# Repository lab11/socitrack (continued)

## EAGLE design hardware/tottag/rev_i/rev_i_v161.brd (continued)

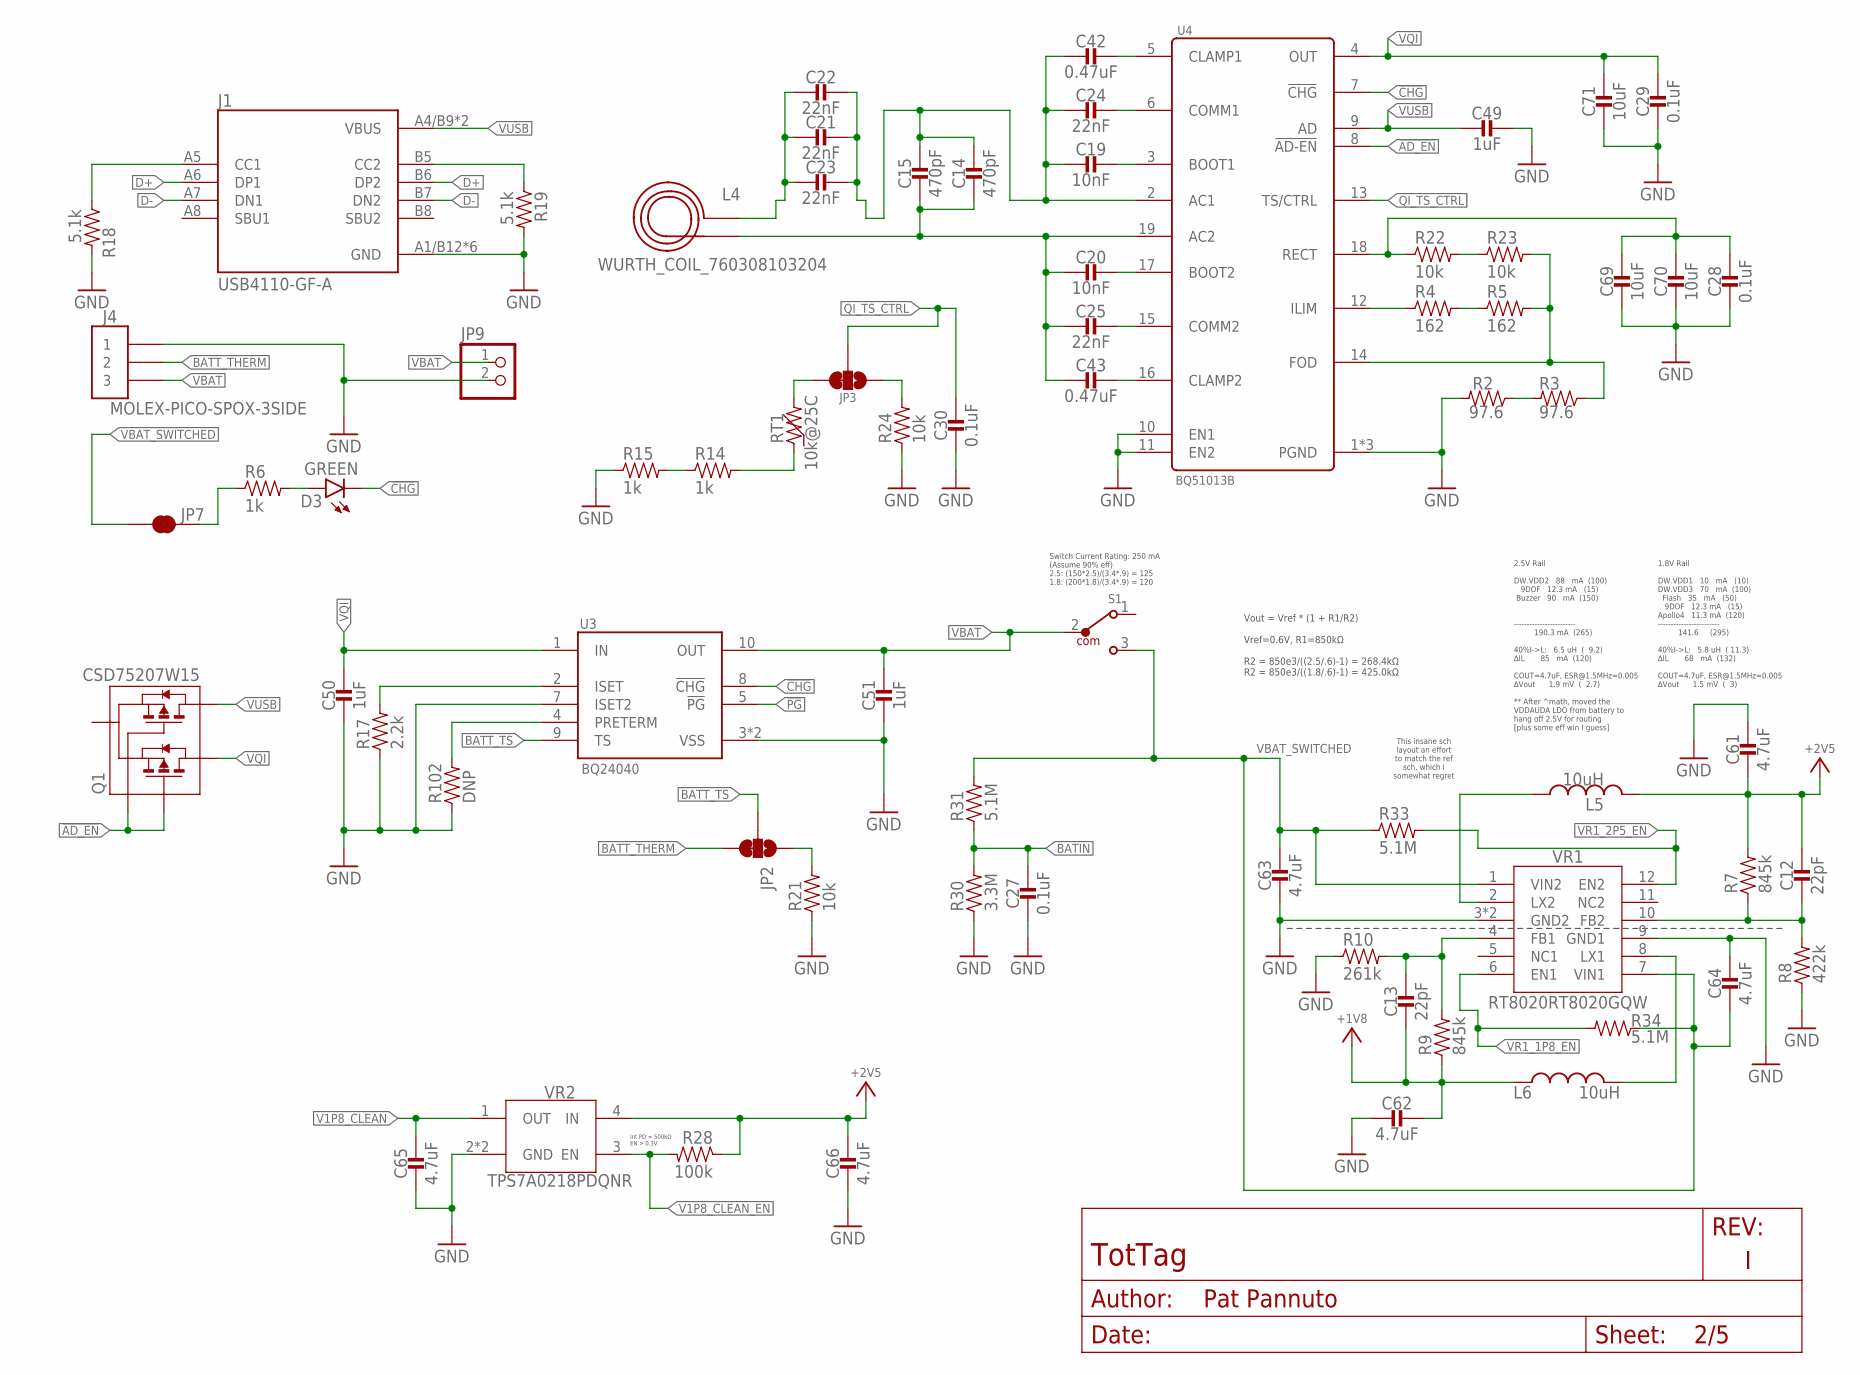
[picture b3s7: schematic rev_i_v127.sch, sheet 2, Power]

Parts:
C12, C13: 22pF; 0201_CAP; MPN GRM0335C1H220FA01D
C14, C15: 470pF; 0402_CAP; MPN GRM1555C1H471JA01J; DIGIKEY 490-6242-1-ND
C19, C20: 10nF; 0402_CAP; MPN GRM155R71H103KA88J; DIGIKEY 490-6351-2-ND
C21, C22, C23: 22nF; 0402_CAP; MPN GRM155R71E223JA61D; DIGIKEY 490-10699-2-ND
C24, C25: 22nF; 0402_CAP; MPN CC0402ZRY5V8BB223; DIGIKEY 311-3823-1-ND
C27, C28, C29, C30: 0.1uF; 0402_CAP; MPN GRM155R71C104KA88J; DIGIKEY 490-6328-1-ND
C42, C43: 0.47uF; 0402_CAP; MPN GRT155R61E474ME01D; DIGIKEY 490-12270-1-ND
C49, C50, C51: 1uF; 0402_CAP; MPN GRM155R70G105KA12D; DIGIKEY 490-7195-1-ND
C61, C62, C63, C64, C65, C66: 4.7uF; 0805_CAP; MPN JMK212ABJ475MGHT
C69, C70, C71: 10uF; 0603_CAP; MPN CM105X5R106M25AT; DIGIKEY 1253-CM105X5R106M25ATCT-ND
D3: GREEN; LED-0603; MPN LTST-C191KGKT; DIGIKEY 160-1446-1-ND
J1: USB4110-GF-A; GCT_USB4110-GF-A
J4: MOLEX-PICO-SPOX-3SIDE; MOLEX-PICO-SPOX-3_SIDE
JP2, JP3: JUMPER-SMT_3_1-NC_TRACE_SILK; SMT-JUMPER_3_1-NC_TRACE_SILK
JP7: JUMPER-SMT_2_NC_TRACE_SILK; SMT-JUMPER_2_NC_TRACE_SILK
JP9: PINHD-1X2; 1X02
L4: WURTH_COIL_760308103204
L5, L6: 10uH; NRX3015; MPN NR3015T100M
Q1: CSD75207W15; DSBGA
R2, R3: 97.6; 0402_RES; MPN RMCF0402FT97R6; DIGIKEY RMCF0402FT97R6CT-ND
R4, R5: 162; 0402_RES; MPN RMCF0402FT162R; DIGIKEY RMCF0402FT162RCT-ND
R6, R14, R15: 1k; 0402_RES
R7, R9: 845k; 0201_RES; MPN ERJ-1GNF8453C
R8: 422k; 0201_RES; MPN ERJ-1GNF4223C
R10: 261k; 0201_RES; MPN ERJ-1GNF2613C
R17: 2.2k; 0402_RES; MPN RMCF0402JT2K20; DIGIKEY RMCF0402JT2K20CT-ND
R18, R19: 5.1k; 0402_RES; MPN RMCF0402FT5K10; DIGIKEY RMCF0402FT5K10CT-ND
R21, R22, R23, R24: 10k; 0402_RES; MPN RC0402JR-0710KL; DIGIKEY 311-10KJRCT-ND
R28: 100k; 0402_RES; MPN RT0402BRE07100KL
R30: 3.3M; 0402_RES; MPN RMCF0402FT3M30; DIGIKEY RMCF0402FT3M30CT-ND
R31, R33, R34: 5.1M; 0402_RES; MPN RMCF0402FT5M10; DIGIKEY RMCF0402FT5M10CT-ND
R102: DNP; 0402_RES
RT1: 10k@25C; 0402_RES; MPN NCU15XH103F60RC; DIGIKEY 490-18149-1-ND
S1: 450404015514; DIGIKEY 732-13665-1-ND
U3: BQ24040; DSQ0010A
U4: BQ51013B; RHL0020A
VR1: RT8020RT8020GQW; SON45P300X300X80-13T160X250N
VR2: TPS7A0218PDQNR; 4-XDFN-EP

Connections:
!AD_EN: Q1.A1 (G1), Q1.C1 (G2), U4.8 (!AD-EN)
!CHG: D3.C, U3.8 (!CHG), U4.7 (!CHG); also elsewhere on the board
!PG: U3.5 (!PG); also elsewhere on the board
+1V8: C13.P$2 (2), C62.P$1 (1), L6.P$1 (1), R9.1; also elsewhere on the board
+2V5: C12.P$1 (1), C61.P$2 (2), C66.P$1 (1), L5.P$2 (2), R7.2, R28.1, VR2.4 (IN); also elsewhere on the board
BATIN: C27.1, R30.2, R31.1; also elsewhere on the board
BATT_THERM: J4.2, J4.2SUPP (2), JP2.3
BATT_TS: JP2.2, U3.9 (TS)
BQ_AC1: C14.1, C15.1, C19.2, C21.1, C22.1, C23.1, C24.2, C42.2, U4.2 (AC1)
BQ_AC2: C14.2, C15.2, C20.2, C25.2, C43.2, L4.P$2 (2), U4.19 (AC2)
BQ_BOOT1: C19.1, U4.3 (BOOT1)
BQ_BOOT2: C20.1, U4.17 (BOOT2)
BQ_CLAMP1: C42.1, U4.5 (CLAMP1)
BQ_CLAMP2: C43.1, U4.16 (CLAMP2)
BQ_COMM1: C24.1, U4.6 (COMM1)
BQ_COMM2: C25.1, U4.15 (COMM2)
BQ_FOD: R3.1, R5.2, R23.2, U4.14 (FOD)
BQ_ILM: R4.1, U4.12 (ILIM)
BQ_ISET: R17.2, U3.2 (ISET)
BQ_RECT: C28.1, C69.1, C70.1, R22.1, U4.18 (RECT)
COIL_AC1: C21.2, C22.2, C23.2, L4.P$1 (1)
D+: J1.A6 (DP1), J1.B6 (DP2)
D-: J1.A7 (DN1), J1.B7 (DN2)
GND: C27.2, C28.2, C29.2, C30.2, C49.1, C50.2, C51.2, C61.P$1 (1), C62.P$2 (2), C63.P$2 (2), C64.P$1 (1), C65.P$2 (2), C66.P$2 (2), C69.2, C70.2, C71.2, J1.A1/B12 (GND), J1.B1/A12 (GND), J1.S1 (GND), J1.S2 (GND), J1.S3 (GND), J1.S4 (GND), J4.1, J4.1SUPP (1), JP9.2, R2.2, R8.1, R10.1, R15.1, R17.1, R18.2, R19.2, R21.1, R24.1, R30.1, R102.1, U3.3 (VSS), U3.7 (ISET2), U3.PAD (VSS), U4.1 (PGND), U4.10 (EN1), U4.11 (EN2), U4.20 (PGND), U4.PAD (PGND), VR1.3 (GND2), VR1.9 (GND1), VR1.13 (GND2), VR2.2 (GND), VR2.PAD (GND); also elsewhere on the board
unnamed: J1.B5 (CC2), R19.1
unnamed: J1.A5 (CC1), R18.1
unnamed: R2.1, R3.2
unnamed: JP2.1, R21.2
unnamed: R102.2, U3.4 (PRETERM)
unnamed: D3.A, R6.2
unnamed: R22.2, R23.1
unnamed: R4.2, R5.1
unnamed: JP3.1, R24.2
unnamed: JP3.3, RT1.2
unnamed: R14.2, RT1.1
unnamed: R14.1, R15.2
QI_TS_CTRL: C30.1, JP3.2, U4.13 (TS/CTRL); also elsewhere on the board
V1P8_CLEAN: C65.P$1 (1), VR2.1 (OUT); also elsewhere on the board
V1P8_CLEAN_EN: R28.2, VR2.3 (EN); also elsewhere on the board
VBAT: C51.1, J4.3, J4.3SUPP (3), JP9.1, S1.2, U3.10 (OUT)
VBAT_SWITCHED: C63.P$1 (1), C64.P$2 (2), JP7.1, R31.2, R33.1, R34.1, S1.3, VR1.1 (VIN2), VR1.7 (VIN1); also elsewhere on the board
VBAT_SW_FOR_CHGLED: JP7.2, R6.1
VQI: C29.1, C50.1, C71.1, Q1.A2 (D1), Q1.A3 (D1), Q1.B3 (D1), U3.1 (IN), U4.4 (OUT)
VR1_1P8_EN: R34.2, VR1.6 (EN1)
VR1_2P5_EN: R33.2, VR1.12 (EN2); also elsewhere on the board
VR1_FB1: C13.P$1 (1), R9.2, R10.2, VR1.4 (FB1)
VR1_FB2: C12.P$2 (2), R7.1, R8.2, VR1.10 (FB2)
VR1_LX1: L6.P$2 (2), VR1.8 (LX1)
VR1_LX2: L5.P$1 (1), VR1.2 (LX2)
VUSB: C49.2, J1.A4/B9 (VBUS), J1.B4/A9 (VBUS), Q1.B2 (D2), Q1.C2 (D2), Q1.C3 (D2), U4.9 (AD)

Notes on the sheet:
2.5V Rail DW.VDD2 88 mA (100) 9DOF 12.3 mA (15) Buzzer 90 mA (150) ------------------------ 190.3 mA (265) 40%I->L: 6.5 uH ( 9.2) ∆IL 85 mA (120) COUT=4.7uF, ESR@1.5MHz=0.005 ∆Vout 1.9 mV ( 2.7) ** After ^math, moved the VDDAUDA LDO from battery to hang off 2.5V for routing [plus some eff win I gue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
1.8V Rail DW.VDD1 10 mA (10) DW.VDD3 70 mA (100) Flash 35 mA (50) 9DOF 12.3 mA (15) Apollo4 11.3 mA (120) ------------------------ 141.6 (295) 40%I->L: 5.8 uH ( 11.3) ∆IL 68 mA (132) COUT=4.7uF, ESR@1.5MHz=0.005 ∆Vout 1.5 mV ( 3)
Vout = Vref * (1 + R1/R2) Vref=0.6V, R1=850kΩ R2 = 850e3/((2.5/.6)-1) = 268.4kΩ R2 = 850e3/((1.8/.6)-1) = 425.0kΩ
This insane sch layout an effort to match the ref sch, which I somewhat regret
Int PD = 500kΩ EN > 0.3V
Switch Current Rating: 250 mA (Assume 90% eff) 2.5: (150*2.5)/(3.4*.9) = 125 1.8: (200*1.8)/(3.4*.9) = 120

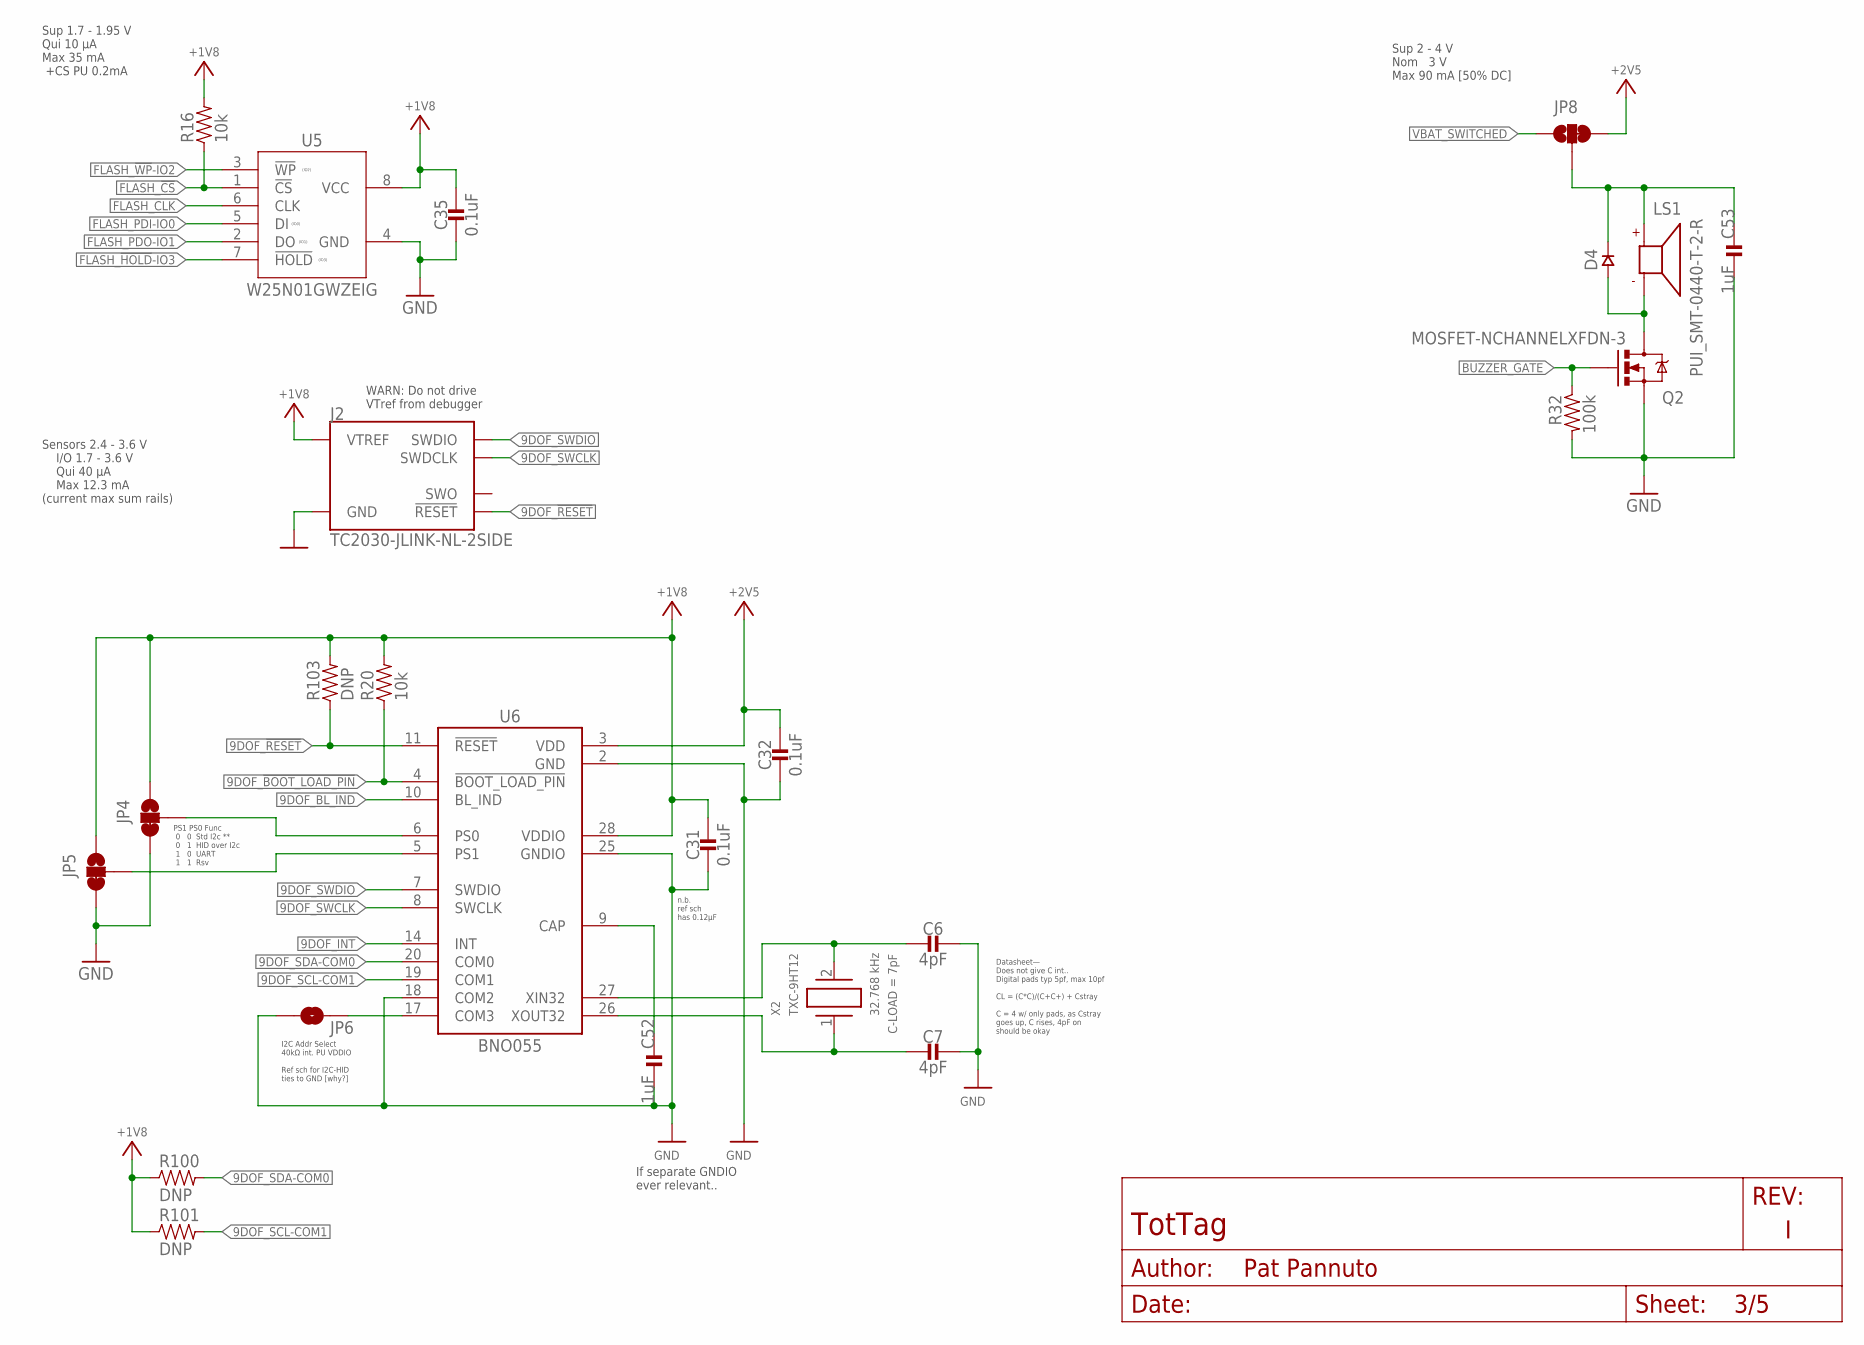
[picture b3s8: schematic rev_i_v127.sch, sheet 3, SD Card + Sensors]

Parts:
C6, C7: 4pF; 0201_CAP; MPN GRM0335C1H4R0BA01D
C31, C32, C35: 0.1uF; 0402_CAP; MPN CL05A104KP5NNNC
C52, C53: 1uF; 0201_CAP; MPN GRM033R61A105ME44D
D4: DIODE0402; 0402_DIODE; MPN CDSQR400B-HF; DIGIKEY 641-2087-1-ND
J2: TC2030-JLINK-NL-2SIDE; TC2030-IDC-NL-2SIDE
JP4, JP5, JP8: JUMPER-SMT_3_1-NC_TRACE_SILK; SMT-JUMPER_3_1-NC_TRACE_SILK
JP6: JUMPER-SMT_2_NO_SILK; SMT-JUMPER_2_NO_SILK
LS1: PUI_SMT-0440-T-2-R; SMT-0440-T-2-R
Q2: MOSFET-NCHANNELXFDN-3; XFDFN-3
R16, R20: 10k; 0402_RES; MPN RC0402JR-0710KL; DIGIKEY 311-10KJRCT-ND
R32: 100k; 0402_RES; MPN RT0402BRE07100KL
R100, R101, R103: DNP; 0603-RES
U5: W25N01GWZEIG; WSON127P800X600X80-9T430X340N
U6: BNO055; LGA28R0P510X4_5P2X3P8X1
X2: TXC-9HT12; MPN 9HT12-32.768KDZY-T

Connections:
9DOF_!BOOT_LOAD_PIN: R20.1, U6.4 (!BOOT_LOAD_PIN); also elsewhere on the board
9DOF_!RESET: J2.3 (!RESET), J2.B3 (!RESET), R103.1, U6.11 (!RESET); also elsewhere on the board
9DOF_BL_IND: U6.10 (BL_IND); also elsewhere on the board
9DOF_CAP: C52.P$1 (1), U6.9 (CAP)
9DOF_INT: U6.14 (INT); also elsewhere on the board
9DOF_SCL-COM1: R101.2, U6.19 (COM1); also elsewhere on the board
9DOF_SDA-COM0: R100.2, U6.20 (COM0); also elsewhere on the board
9DOF_SWCLK: J2.4 (SWDCLK), J2.B4 (SWDCLK), U6.8 (SWCLK)
9DOF_SWDIO: J2.2 (SWDIO), J2.B2 (SWDIO), U6.7 (SWDIO)
9DOF_XI: C6.P$2 (2), U6.27 (XIN32), X2.2
9DOF_XO: C7.P$2 (2), U6.26 (XOUT32), X2.1
+1V8: C31.1, C35.1, J2.1 (VTREF), J2.B1 (VTREF), JP4.1, JP5.1, R16.2, R20.2, R100.1, R101.1, R103.2, U5.8 (VCC), U6.28 (VDDIO); also elsewhere on the board
+2V5: C32.1, JP8.3, U6.3 (VDD); also elsewhere on the board
BUZZER_GATE: Q2.G, R32.1; also elsewhere on the board
BUZZER_SUPPLY: C53.P$1 (1), D4.CATHODE, JP8.2, LS1.+
FLASH_!CS: R16.1, U5.1 (!CS); also elsewhere on the board
FLASH_!HOLD!-IO3: U5.7 (!HOLD); also elsewhere on the board
FLASH_!WP!-IO2: U5.3 (!WP); also elsewhere on the board
FLASH_CLK: U5.6 (CLK); also elsewhere on the board
FLASH_PDI-IO0: U5.5 (DI); also elsewhere on the board
FLASH_PDO-IO1: U5.2 (DO); also elsewhere on the board
GND: C6.P$1 (1), C7.P$1 (1), C31.2, C32.2, C35.2, C52.P$2 (2), C53.P$2 (2), J2.5 (GND), J2.B5 (GND), JP4.3, JP5.3, JP6.1, Q2.S, R32.2, U5.4 (GND), U6.2 (GND), U6.18 (COM2), U6.25 (GNDIO); also elsewhere on the board
unnamed: D4.ANODE, LS1.- (N), Q2.D
unnamed: JP4.2, U6.6 (PS0)
unnamed: JP5.2, U6.5 (PS1)
unnamed: JP6.2, U6.17 (COM3)
VBAT_SWITCHED: JP8.1; also elsewhere on the board

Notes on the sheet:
Sup 1.7 - 1.95 V Qui 10 µA Max 35 mA +CS PU 0.2mA
Sensors 2.4 - 3.6 V I/O 1.7 - 3.6 V Qui 40 µA Max 12.3 mA (current max sum rails)
Sup 2 - 4 V Nom 3 V Max 90 mA [50% DC]
PS1 PS0 Func 0 0 Std I2c ** 0 1 HID over I2c 1 0 UART 1 1 Rsv
If separate GNDIO ever relevant..
I2C Addr Select 40kΩ int. PU VDDIO Ref sch for I2C-HID ties to GND [why?]
n.b. ref sch has 0.12µF
WARN: Do not drive VTref from debugger
Datasheet— Does not give C int.. Digital pads typ 5pf, max 10pf CL = (C*C)/(C+C+) + Cstray C = 4 w/ only pads, as Cstray goes up, C rises, 4pF on should be okay

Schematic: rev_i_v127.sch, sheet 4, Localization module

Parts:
A1, A2, A3: ACR0301U
C3: 2pF; 0201_CAP; MPN CBR02C209A5GAC
C10, C11: 12pF; 0402_CAP; MPN CBR04C120F5GAC; DIGIKEY 399-8815-2-ND
C16, C17, C18: 4.7nF; 0402_CAP; MPN C0402C472K3RAC7867
C33, C34, C36, C37, C38, C39: 0.1uF; 0402_CAP; MPN CL05A104KP5NNNC
C40, C41: 0.22uF; 0402_CAP; MPN CL05A224KP5NNNC
C67, C68: 4.7uF; 0402_CAP; MPN CL05A475MP5NRNC
C72, C73: 10uF; 0603_CAP; MPN CM105X5R106M25AT; DIGIKEY 1253-CM105X5R106M25ATCT-ND
FB1: BLM03PG330SN1D; 0201_FB; MPN BLM03PG330SN1D
R1: 49.9-1%; 0201_RES; MPN ERJ-1GNF49R9C
R29: 100k; 0402_RES; MPN RT0402BRE07100KL
S2: SKY13373
S3: SIP3241XSIP32414; TDFN2X2X0P6-8
TP0, TP1, TP2, TP3, TP4, TP5, TP6, TP7: TEST-POINT; PAD.03X.03
U2: DW3210; QFN40P500X500X80-40N
X4: 38.4MHz; FA-20H; MPN FA-20H 38.4000MF10Z-AS3; DIGIKEY SER3631CT-ND

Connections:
!DW_RST: U2.33 (!RST); also elsewhere on the board
!DW_SPI_CS: U2.37 (!SPICS); also elsewhere on the board
+1V8: C41.1, C68.2, S3.4 (IN), U2.29 (VDD1); also elsewhere on the board
+2V5: C34.1, C67.2, S2.6 (VDD), S3.1 (IN); also elsewhere on the board
DW_EXTON: S3.2 (CTL), S3.3 (CTL), U2.31 (EXTON)
DW_GPIO4: TP4.P$1, U2.8 (GPIO4/EXTPA)
DW_GPIO5: TP5.P$1, U2.5 (GPIO5/EXTTXE/SPIPOL)
DW_GPIO6: TP6.P$1, U2.2 (GPIO6/EXTRXE/SPIPHA)
DW_IRQ: R29.2, U2.1 (IRQ/GPIO8); also elsewhere on the board
DW_RF1: C3.P$1 (1), U2.18 (RF1)
DW_RF2: R1.1, U2.13 (RF2)
DW_RXLED: TP2.P$1, U2.6 (GPIO2/RXLED)
DW_RXOKLED: TP0.P$1, U2.3 (GPIO0/RXOKLED)
DW_SFDLED: TP1.P$1, U2.4 (GPIO1/SFDLED)
DW_SPI_CIPO: U2.36 (SPICDO(MISO)); also elsewhere on the board
DW_SPI_CLK: U2.34 (SPICLK); also elsewhere on the board
DW_SPI_COPI: U2.35 (SPICDI(MOSI)); also elsewhere on the board
DW_SYNC: TP7.P$1, U2.9 (GPIO7/SYNC)
DW_TXLED: TP3.P$1, U2.7 (GPIO3/TXLED)
DW_VDD2A: C16.1, FB1.P$2, U2.28 (VDD2A)
DW_VDD2_SUP: C17.1, C33.1, C37.1, C73.1, FB1.P$1, S3.8 (OUT), U2.23 (VDD2B)
DW_VDD3_SUP: C18.1, C36.1, C39.1, C72.1, S3.5 (OUT), U2.26 (VDD3)
DW_VIO_D: C38.1, U2.38 (VIO_D)
DW_VTX_D: C40.1, U2.27 (VTX_D)
DW_WAKEUP: U2.32 (WAKEUP); also elsewhere on the board
DW_XTI: C11.1, U2.21 (XTI), X4.3 (2)
DW_XTO: C10.1, U2.22 (XTO), X4.1
GND: C10.2, C11.2, C16.2, C17.2, C18.2, C33.2, C34.2, C36.2, C37.2, C38.2, C39.2, C40.2, C41.2, C67.1, C68.1, C72.2, C73.2, R1.2, R29.1, S2.2 (GND), S2.7 (GND), S2.8 (GND), S2.10 (GND), S2.12 (GND), S2.PAD (GND), S3.6 (GND), S3.7 (GND), S3.PAD (GND), U2.10 (GND-RF), U2.11 (GND-RF), U2.12 (GND-RF), U2.14 (GND-RF), U2.15 (GND-RF), U2.16 (GND-RF), U2.17 (GND-RF), U2.19 (GND-RF), U2.20 (GND-RF), U2.24 (VSS2), U2.25 (VSS3), U2.30 (VSS1), U2.39 (VSS), U2.40 (VSS), X4.2 (GND), X4.4 (GND); also elsewhere on the board
RF1: A1.FEED, S2.9 (J2)
RF2: A2.FEED, S2.3 (J3)
RF3: A3.FEED, S2.1 (J1)
RFC: C3.P$2 (2), S2.11 (RFC)
RFSW_V1: S2.4 (V1); also elsewhere on the board
RFSW_V2: S2.5 (V2); also elsewhere on the board

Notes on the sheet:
Supply 2.4 - 3.6 V ds #'s @ 3.0 V min typ max VDD1 1.6 3.0 3.6 VDD2a,b 2.4 3.0 3.6 VDD3 1.5 3.0 3.6 Voltage on GPIO0-5, WAKEUP, RSTn, SPICSn, SPIMOSI, SPICLK -> Max: VDD1+0.3V I/O current (max): 10 mA VDD1 -> I/O Peak cont current is RX CH9: 88 mA TX worst-case: VDD2a/b: 20 mA VDD3: 20 mA RX worst-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
SupV 2.5-4.8 I/O V 1.65-min(3.3,SupV) Active: 60 µA Qui: 5 µA
V1 V2 State 0 0 Shutdown 1 0 RFC<>J2 0 1 RFC<>J1 1 1 RFC<>J3

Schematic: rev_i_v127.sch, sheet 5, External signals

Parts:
FD1, FD2, FD3: FIDUCIAL1X2; FIDUCIAL-1X2
TP8, TP9, TP10, TP11, TP12, TP13, TP14, TP15, TP16, TP17, TP18, TP19, TP20: TEST-POINT; PAD.03X.03
TP_DW_CIPO: TPTP06SQ; TP06SQ
TP_DW_COPI: TPTP06SQ; TP06SQ
TP_DW_SPI_CLK: TPTP06SQ; TP06SQ
TP_DW_SPI_CS: TPTP06SQ; TP06SQ

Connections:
9DOF_INT: TP17.P$1; also elsewhere on the board
9DOF_SCL-COM1: TP18.P$1; also elsewhere on the board
9DOF_SDA-COM0: TP19.P$1; also elsewhere on the board
!DW_SPI_CS: TP_DW_SPI_CS.TP; also elsewhere on the board
AP4_LED1_GREEN: TP10.P$1; also elsewhere on the board
AP4_LED1_RED: TP20.P$1; also elsewhere on the board
AP4_LED2_RED: TP11.P$1; also elsewhere on the board
AP4_LED2_YELLOW: TP12.P$1; also elsewhere on the board
DW_SPI_CIPO: TP_DW_CIPO.TP; also elsewhere on the board
DW_SPI_CLK: TP_DW_SPI_CLK.TP; also elsewhere on the board
DW_SPI_COPI: TP_DW_COPI.TP; also elsewhere on the board
FLASH_!CS: TP8.P$1; also elsewhere on the board
FLASH_!HOLD!-IO3: TP16.P$1; also elsewhere on the board
FLASH_!WP!-IO2: TP15.P$1; also elsewhere on the board
FLASH_CLK: TP9.P$1; also elsewhere on the board
FLASH_PDI-IO0: TP13.P$1; also elsewhere on the board
FLASH_PDO-IO1: TP14.P$1; also elsewhere on the board

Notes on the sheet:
Miscellany
Fiducials

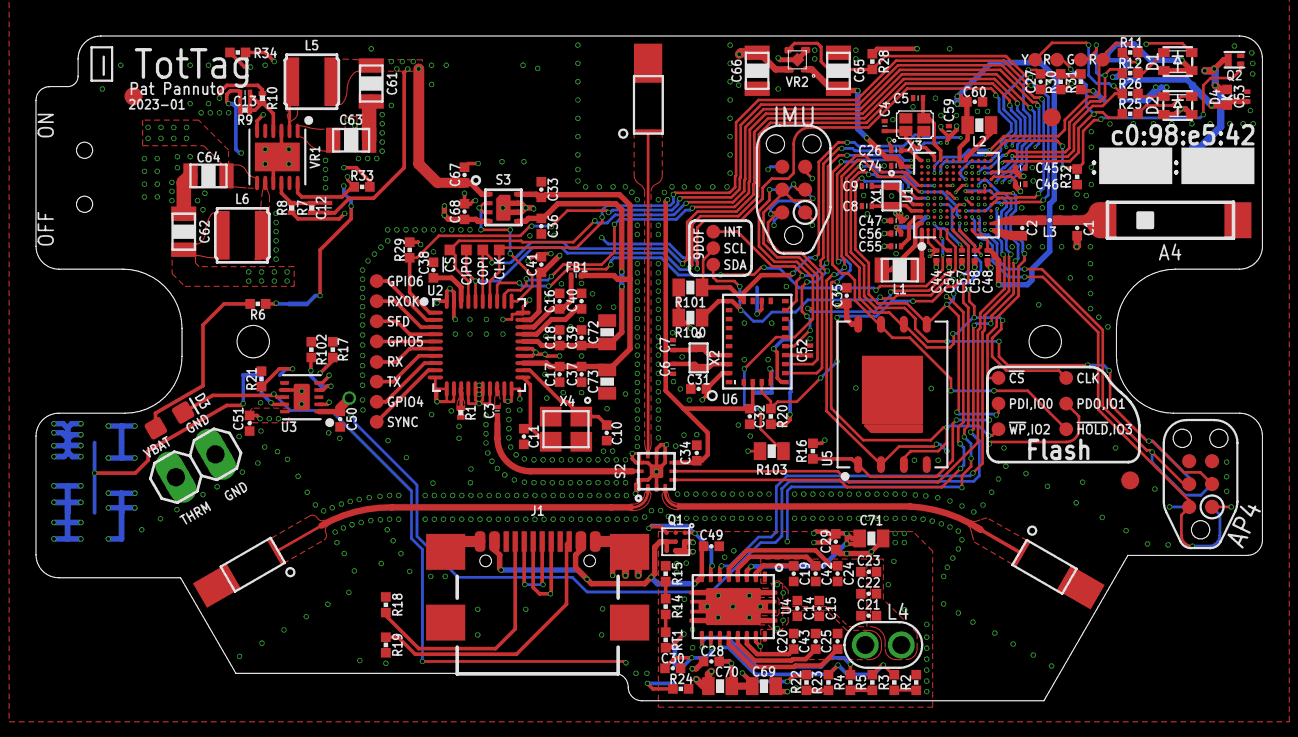
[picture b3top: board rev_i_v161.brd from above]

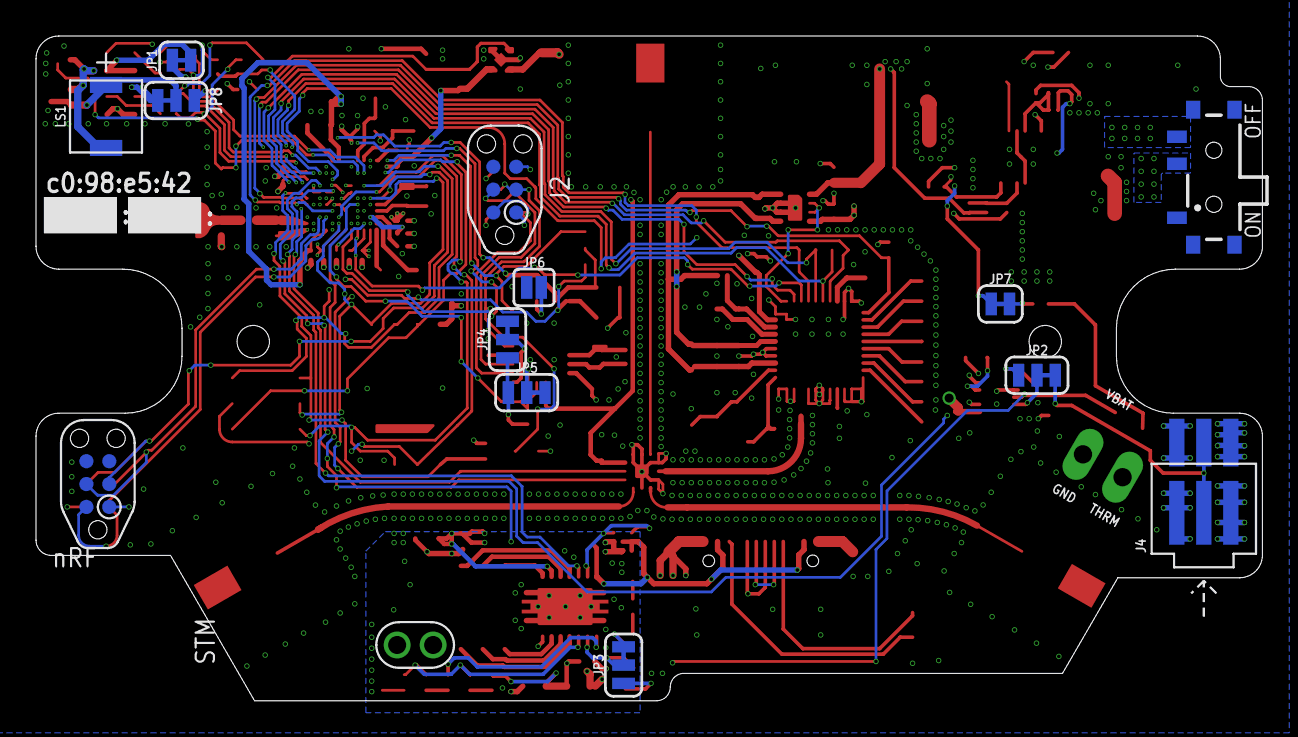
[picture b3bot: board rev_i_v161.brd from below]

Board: 4 copper layers, 68.1 x 36.9 mm, 185 parts (11 on the bottom side), 131 nets.

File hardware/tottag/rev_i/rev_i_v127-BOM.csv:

Qty,Value,Device,Package,Parts,Description,DIGIKEY,MANUFACTURER,MPN
3,ACR0301U,ACR0301U,ACR0301U,"A1, A2, A3",,,Abracon,ACR0301U
1,AMCA72-2R47G-S1F-T,AMCA72-2R47G-S1F-T,AMCA72-2R470G-S1F-T,A4,RF ANT 2.4GHZ CHIP SOLDER SMD,535-14108-1-ND,,AMCA72-2R470G-S1F-T4
1,0.5pF,CAPACITOR0402_CAP,0402_CAP,C1,SMD Capacitor,,,GJM1555C1HR50WB01D
1,0.8pF,CAPACITOR0402_CAP,0402_CAP,C2,SMD Capacitor,,,GJM1555C1HR80WB01D
1,2pF,CAPACITOR0201_CAP,0201_CAP,C3,SMD Capacitor,,,CBR02C209A5GAC
4,4pF,CAPACITOR0201_CAP,0201_CAP,"C4, C5, C6, C7",SMD Capacitor,,Murata,GRM0335C1H4R0BA01D
2,6pF,CAPACITOR0201_CAP,0201_CAP,"C8, C9",SMD Capacitor,,Murata,GRM0335C1H6R0BA01D
2,12pF,CAPACITOR0402_CAP,0402_CAP,"C10, C11",SMD Capacitor,399-8815-2-ND,,CBR04C120F5GAC
2,22pF,CAPACITOR0201_CAP,0201_CAP,"C12, C13",SMD Capacitor,,,GRM0335C1H220FA01D
2,470pF,CAPACITOR0402_CAP,0402_CAP,"C14, C15",SMD Capacitor,490-6242-1-ND,Murata,GRM1555C1H471JA01J
3,4.7nF,CAPACITOR0402_CAP,0402_CAP,"C16, C17, C18",SMD Capacitor,,,C0402C472K3RACTU
2,10nF,CAPACITOR0402_CAP,0402_CAP,"C19, C20",SMD Capacitor,490-6351-2-ND,,GRM155R71H103KA88J
3,22nF,CAPACITOR0402_CAP,0402_CAP,"C21, C22, C23",SMD Capacitor,490-10699-2-ND,,GRM155R71E223JA61D
2,22nF,CAPACITOR0402_CAP,0402_CAP,"C24, C25",SMD Capacitor,311-3823-1-ND,,CC0402ZRY5V8BB223
1,0.1uF,CAPACITOR0201_CAP,0201_CAP,C26,SMD Capacitor,,,CL05A104KP5NNNC
4,0.1uF,CAPACITOR0402_CAP,0402_CAP,"C27, C28, C29, C30",SMD Capacitor,490-6328-1-ND,,GRM155R71C104KA88J 
9,0.1uF,CAPACITOR0402_CAP,0402_CAP,"C31, C32, C33, C34, C35, C36, C37, C38, C39",SMD Capacitor,,,CL05A104KP5NNNC
2,0.22uF,CAPACITOR0402_CAP,0402_CAP,"C40, C41",SMD Capacitor,,,CL05A224KP5NNNC
2,0.47uF,CAPACITOR0402_CAP,0402_CAP,"C42, C43",SMD Capacitor,490-12270-1-ND,,GRT155R61E474ME01D
8,1uF,CAPACITOR0201_CAP,0201_CAP,"C44, C45, C46, C47, C48, C52, C53, C74",SMD Capacitor,,Murata,GRM033R61A105ME44D
3,1uF,CAPACITOR0402_CAP,0402_CAP,"C49, C50, C51",SMD Capacitor,,,GRM155R70J105KA12J
6,2.2uF,CAPACITOR0201_CAP,0201_CAP,"C54, C55, C56, C57, C58, C59",SMD Capacitor,,Murata,GRM033R61A225KE47D
3,4.7uF,CAPACITOR0402_CAP,0402_CAP,"C60, C67, C68",SMD Capacitor,,,CL05A475MP5NRNC
6,4.7uF,CAPACITOR0805_CAP,0805_CAP,"C61, C62, C63, C64, C65, C66",SMD Capacitor,,Taiyo Yuden,JMK212ABJ475MGHT
5,10uF,CAPACITOR0603_CAP,0603_CAP,"C69, C70, C71, C72, C73",SMD Capacitor,1253-CM105X5R106M25ATCT-ND,,CM105X5R106M25AT
1,BICOLOR-SMD,BICOLOR-SMD,LED-0606,D1,,,,MCL0606FRD1GR1T
1,BICOLOR-SMD,BICOLOR-SMD,LED-0606,D2,,,,MCL0606FYW1RD1T
1,GREEN,LED0603,LED-0603,D3,LED (Generic),160-1446-1-ND,,LTST-C191KGKT
1,DIODE0402,DIODE0402,0402_DIODE,D4,,641-2087-1-ND,,CDSQR400B-HF
1,BLM03PG330SN1D,FERRITE_BEAD0201,0201_FB,FB1,,,Murata,BLM03PG330SN1D
DNP,FIDUCIAL1X2,FIDUCIAL1X2,FIDUCIAL-1X2,"FD1, FD2, FD3",Fiducial Alignment Points,,,
1,USB4110-GF-A,USB4110-GF-A,GCT_USB4110-GF-A,J1," USB-C (USB TYPE-C) USB 2.0 Receptacle Connector 24 (16+8 Dummy) Position Surface Mount, Right Angle", Through Hole ,,USB4110-GF-A
DNP,TC2030-JLINK-NL-2SIDE,TC2030-JLINK-NL-2SIDE,TC2030-IDC-NL-2SIDE,"J2, J3",,,,
1,MOLEX-PICO-SPOX-3SIDE,MOLEX-PICO-SPOX-3SIDE,MOLEX-PICO-SPOX-3_SIDE,J4,MOLEX,WM7647CT-ND,,
DNP,JUMPER-SMT_2_NC_TRACE_SILK,JUMPER-SMT_2_NC_TRACE_SILK,SMT-JUMPER_2_NC_TRACE_SILK,"JP1, JP7",Normally closed trace jumper,,,
DNP,JUMPER-SMT_3_1-NC_TRACE_SILK,JUMPER-SMT_3_1-NC_TRACE_SILK,SMT-JUMPER_3_1-NC_TRACE_SILK,"JP2, JP3, JP4, JP5, JP8",Normally closed trace jumper (1 of 2 connections),,,
DNP,JUMPER-SMT_2_NO_SILK,JUMPER-SMT_2_NO_SILK,SMT-JUMPER_2_NO_SILK,JP6,Normally open jumper,,,
DNP,,PINHD-1X2,1X02,JP9,PIN HEADER,,,
1,2.2µH,INDUCTOR0805,0805_CAP,L1,A very specific inductor,,Murata,DFE201210U-2R2M=P2
1,1.0µH,INDUCTOR0603,0603_CAP,L2,A very specific inductor,,Murata,DFE18SAN1R0ME0L
1,4.7nH,INDUCTOR0402,0402_CAP,L3,A very specific inductor,,,LQW15AN4N7G8ZD
1,WURTH_COIL_760308103204,WURTH_COIL_760308103204,WURTH_COIL_760308103204,L4,,732-5258-ND,Würth Elektronik,7.60308E+11
2,10uH,INDUCTORNRX3015,NRX3015,"L5, L6",A very specific inductor,,TAIYO YUDEN,NR3015T100M
1,PUI_SMT-0440-T-2-R,PUI_SMT-0440-T-2-R,SMT-0440-T-2-R,LS1,,668-SMT-0440-T-2-RTR-ND,,SMT-0440-T-2-R
1,CSD75207W15,CSD75207W15,DSBGA,Q1,"low on resistance, gate charge dual p-channel nexfet",296-40008-1-ND,TEXAS INSTRUMENTS,CSD75207W15
1,MOSFET-NCHANNELXFDN-3,MOSFET-NCHANNELXFDN-3,XFDFN-3,Q2,Generic NMOS footprint,DMN2400UFB4-7DICT-ND,,
1,49.9-1%,RESISTOR0201_RES,0201_RES,R1,Resistor,,,ERJ-1GNF49R9C
2,97.6,RESISTOR0402_RES,0402_RES,"R2, R3",Resistor,RMCF0402FT97R6CT-ND,,RMCF0402FT97R6
2,162,RESISTOR0402_RES,0402_RES,"R4, R5",Resistor,RMCF0402FT162RCT-ND,,RMCF0402FT162R
3,1k,RESISTOR0402_RES,0402_RES,"R6, R14, R15",Resistor,,,RC0402JR-071KL
2,845k,RESISTOR0201_RES,0201_RES,"R7, R9",Resistor,,,ERJ-1GNF8453C
1,422k,RESISTOR0201_RES,0201_RES,R8,Resistor,,,ERJ-1GNF4223C
1,261k,RESISTOR0201_RES,0201_RES,R10,Resistor,,,ERJ-1GNF2613C
2,15,RESISTOR0402_RES,0402_RES,"R11, R25",Resistor,,,RC0402JR-0715RL
2,5.1,RESISTOR0402_RES,0402_RES,"R12, R26",Resistor,,,RC0402JR-075R1L
6,10k,RESISTOR0402_RES,0402_RES,"R16, R20, R21, R22, R23, R24",Resistor,311-10KJRCT-ND ,,RC0402JR-0710KL
1,2.2k,RESISTOR0402_RES,0402_RES,R17,Resistor,RMCF0402JT2K20CT-ND,,RMCF0402JT2K20
2,5.1k,RESISTOR0402_RES,0402_RES,"R18, R19",Resistor,RMCF0402FT5K10CT-ND,,RMCF0402FT5K10
3,100k,RESISTOR0402_RES,0402_RES,"R28, R29, R32",Resistor,,,RT0402BRE07100KL
1,3.3M,RESISTOR0402_RES,0402_RES,R30,Resistor,RMCF0402FT3M30CT-ND,,RMCF0402FT3M30
3,5.1M,RESISTOR0402_RES,0402_RES,"R31, R33, R34",Resistor,RMCF0402FT5M10CT-ND,,RMCF0402FT5M10
DNP,DNP,RESISTOR0603_RES,0603-RES,"R100, R101, R103",Resistor,,,
DNP,DNP,RESISTOR0402_RES,0402_RES,R102,Resistor,,,
1,10k@25C,THERMISTOR0402,0402_RES,RT1,Thermistor.,490-18149-1-ND,,NCU15XH103F60RC
1,,4.50404E+11,4.50404E+11,S1,"WS-SLSU Mini Slide Switch, Same Side Connection Side Push 6.7x2.7 mm",732-13665-1-ND,,
1,SKY13373,SKY13373,SKY13373,S2,0.1 to 8.0 GHz SP3T Switch,,Skyworks,SKY13373-460LF
1,SIP3241XSIP32414,SIP3241XSIP32414,TDFN2X2X0P6-8,S3,,,Vishay,SIP32414DNP-T1-GE4
DNP,TPTP06SQ,TPTP06SQ,TP06SQ,"TP_DW_CIPO, TP_DW_COPI, TP_DW_SPI_CLK, TP_DW_SPI_CS",Test pad,,,
DNP,TEST-POINT,TEST-POINT,PAD.03X.03,"TP0, TP1, TP2, TP3, TP4, TP5, TP6, TP7, TP8, TP9, TP10, TP11, TP12, TP13, TP14, TP15, TP16, TP17, TP18, TP19, TP20",,,,
1,APOLLO4_BLUE_SOC_BGA,APOLLO4_BLUE_SOC_BGA,APOLLO4_BLUE_SOC_BGA,U1,,,ambiq,AMA4B2KK-KBR
1,DW3210,DW3210,QFN40P500X500X80-40N,U2,DW3000 QFN No PDoA,,Qorvo,DW3210
1,BQ24040,BQ24040,DSQ0010A,U3,Simple Li Ion / Li Poly charger.,296-37142-1-ND,,BQ24040DSQR
1,BQ51013B,BQ51013B,RHL0020A,U4,bq51013B,296-38885-1-ND,,BQ51013BRHLR
1,W25N01GWZEIG,W25N01GWZEIG,WSON127P800X600X80-9T430X340N,U5,,,Winbond,W25N01GWZEIG
1,BNO055,BNO055,LGA28R0P510X4_5P2X3P8X1,U6,,,Bosch Scientific,BNO055
1,RT8020RT8020GQW,RT8020RT8020GQW,SON45P300X300X80-13T160X250N,VR1,,,RichTek,RT8020GQW
1,TPS7A0218PDQNR,TPS7A0218PDQNR,4-XDFN-EP,VR2,,,,TPS7A0218PDQNR
2,TXC-9HT12,TXC-9HT12,TXC-9HT12,"X1, X2",,,TXC Corp,9HT12-32.768KDZY-T
1,ABM12W,ABM12W,ABM12W,X3,,,Abracon,ABM12W-32.0000MHZ-6-D1X-T3
1,38.4MHz,FA-20H,FA-20H,X4,"38.4MHz ±10ppm Crystal 8.5pF 40 Ohms 4-SMD, No Lead",SER3631CT-ND,EPSON,FA-20H 38.4000MF10Z-AS3
